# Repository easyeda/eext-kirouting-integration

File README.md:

# KiRouting Integration

[English](README_EN.md) | 中文

将 **KiCadRouting Tools**（Rust 加速 A* 自动布线引擎）桥接到 **嘉立创EDA专业版（EasyEDA Pro）** 的完整解决方案。

## 项目地址

| 项目 | 地址 | 说明 |
|------|------|------|
| 本项目（扩展 + 桥接服务器） | https://github.com/easyeda/eext-kirouting-integration | EasyEDA Pro 扩展及 Python 桥接服务器 |
| KiCadRouting Tools（布线引擎） | https://github.com/drandyhaas/KiCadRoutingTools/tree/main#command-line-interface | Rust 加速 A* 路由器（原项目） |

## 系统架构

```
┌─────────────────────┐     HTTP (localhost:8765)     ┌──────────────────────┐
│  EasyEDA Pro 编辑器  │ ◄──────────────────────────► │   Bridge Server      │
│  (嘉立创EDA专业版)    │                              │   (Python/FastAPI)   │
│                     │                              │                      │
│  ┌───────────────┐  │                              │  ┌────────────────┐  │
│  │ TypeScript 扩展│  │  ← 收集PCB数据 / 写回结果 →   │  │ 格式转换        │  │
│  │ (kirouting-   │  │                              │  │ EasyEDA ↔ KiCad│  │
│  │  integration) │  │                              │  └───────┬────────┘  │
│  └───────────────┘  │                              │          │           │
└─────────────────────┘                              │          ▼           │
                                                     │  ┌────────────────┐  │
                                                     │  │ KiCadRouting   │  │
                                                     │  │ Tools 布线引擎  │  │
                                                     │  │ (Python + Rust)│  │
                                                     │  └────────────────┘  │
                                                     └──────────────────────┘
```

## 快速开始（用户安装）

只需两步即可使用：

### 第一步：安装扩展

在 EasyEDA Pro（嘉立创EDA专业版）的 **扩展广场** 中搜索 **KiRouting Integration** 并安装。

也可以手动安装：从 [GitHub Releases](https://github.com/easyeda/eext-kirouting-integration/releases/latest) 下载 `.eext` 文件，在 **扩展** → **扩展管理器** → **从本地安装** 中导入。

> **重要**：安装后需在 EasyEDA Pro 设置中开启 **外部交互**（External Interaction）选项，否则扩展无法连接本地 KiRouting 服务。

### 第二步：获取启动脚本

从本项目仓库获取桥接服务器：

```bash
git clone https://github.com/easyeda/eext-kirouting-integration.git
```

或直接在 [项目页面](https://github.com/easyeda/eext-kirouting-integration) 点击 **Code** → **Download ZIP** 下载并解压。

启动脚本位于项目目录中的 `bridge_server/start_server.bat`。

### 第三步：启动桥接服务器

双击运行 `bridge_server/start_server.bat`，脚本会自动完成以下操作：

1. 检测 Python 环境，未安装则自动通过 winget 安装
2. 检测并安装 Python 依赖（fastapi、uvicorn、pydantic、numpy）
3. 检测 KiCadRoutingTools，不存在则自动从 GitHub 克隆
4. 检测 Rust 路由器编译产物，未编译则自动构建（无 Rust 环境时降级为纯 Python 模式）
5. 启动桥接服务器（监听 `http://localhost:8765`）

> 首次运行需要联网下载依赖，后续启动会跳过已完成的步骤。

### 第四步：开始使用

1. 打开一个 PCB 文件
2. 顶部菜单栏点击 **KiRouting自动布线** → **打开布线工具...**
3. 在弹出的对话框中选择网络、配置参数、点击 **开始布线**

4. 等待布线完成，结果自动写回 PCB

> 如果服务器未启动，扩展会弹出引导对话框，提供下载链接和操作说明。

## 布线功能

- **单端布线** — A* 寻路，支持 MPS 网络排序、拆线重布、总线检测
- **差分对布线** — 中心线 + 偏移，自动极性交换，GND 过孔放置
- **电源平面** — 自动过孔连接 SMD 焊盘到内层铜皮，Voronoi 分区
- **BGA 扇出** — 自动逃逸路径生成
- **QFN 扇出** — QFN/QFP 焊盘延伸
- **长度匹配** — DDR4 字节通道自动分组，蛇形走线
- **阻抗控制** — 根据叠层自动计算每层线宽
- **目标交换优化** — 匈牙利算法最小化交叉

## 布线工作流程（数据流）

```
1. 扩展从 EasyEDA Pro 读取 PCB 数据（元件、焊盘、网络、已有走线、板框）
       ↓
2. 大型元件列表分块发送 → POST /api/extra-components
       ↓
3. 完整 PCB 数据 + 布线参数 → POST /api/route
       ↓
4. 服务器格式转换：EasyEDA JSON → .kicad_pcb（坐标系、单位、层映射）
       ↓
5. 调用 KiCadRoutingTools 执行 A* 布线
       ↓
6. 对比输入/输出 .kicad_pcb，提取新增走线和过孔
       ↓
7. 转换回 EasyEDA 坐标系
       ↓
8. 扩展轮询 GET /api/status/{job_id} 等待完成
       ↓
9. 扩展获取结果 GET /api/result/{job_id}
       ↓
10. 将新走线/过孔写入 EasyEDA Pro PCB 编辑器
```

## API 接口

| 方法 | 路径 | 说明 |
|------|------|------|
| GET | `/api/test` | 健康检查，确认服务器运行 |
| POST | `/api/extra-components` | 分块发送大型元件列表 |
| POST | `/api/route` | 提交布线任务（异步，返回 job_id） |
| GET | `/api/status/{job_id}` | 查询任务状态 |
| GET | `/api/result/{job_id}` | 获取布线结果（走线 + 过孔） |
| POST | `/api/cancel/{job_id}` | 取消正在运行的任务 |
| GET | `/api/config/defaults` | 获取默认布线参数 |
| POST | `/api/analyze/board-summary` | 板卡概览分析 |
| POST | `/api/analyze/power-nets` | 电源网络分析 |
| POST | `/api/analyze/diff-pairs` | 差分对检测 |
| POST | `/api/analyze/bus-groups` | 总线组检测 |
| POST | `/api/analyze/net-stats` | 网络统计 |

## 开发者指南

以下内容面向需要修改源码或从源码构建的开发者。

### 目录结构

```
KICAD Routing-intergration/
├── KiCadRoutingTools/              # 布线引擎（Rust加速A*路由器）
│   ├── route.py                    # 单端布线 CLI
│   ├── route_diff.py               # 差分对布线 CLI
│   ├── route_planes.py             # 电源/地平面 CLI
│   ├── rust_router/                # Rust A* 实现
│   └── ...
├── kirouting-integration/           # EasyEDA Pro 扩展 + 桥接服务器
│   ├── src/index.ts                # 扩展入口（TypeScript）
│   ├── iframe/                     # 扩展 UI（参数配置对话框）
│   ├── bridge_server/              # Python 桥接服务器
│   │   ├── server.py               # FastAPI 服务（端口 8765）
│   │   ├── start_server.bat        # 一键启动脚本（自动安装依赖）
│   │   ├── routing_runner.py       # 布线调度（调用 KiCadRoutingTools）
│   │   ├── easyeda_to_kicad.py     # EasyEDA JSON → KiCad 格式转换
│   │   ├── kicad_diff.py           # 对比输入/输出提取新走线
│   │   ├── coord_transform.py      # 坐标系转换（mil ↔ mm）
│   │   ├── layer_mapping.py        # 层映射（EasyEDA ↔ KiCad）
│   │   ├── models.py               # Pydantic 数据模型
│   │   ├── analysis.py             # AI 分析（电源网络、差分对等）
│   │   └── requirements.txt        # Python 依赖
│   ├── extension.json              # 扩展清单
│   ├── package.json                # Node.js 项目配置
│   └── tsconfig.json               # TypeScript 配置
└── README.md                       # 本文件
```

### 环境要求

| 组件 | 版本要求 | 用途 |
|------|---------|------|
| Python | 3.8+ | 桥接服务器 |
| Node.js | 20.5.0+ | 编译扩展 |
| Rust | stable | 编译路由器（可选，无则降级为纯 Python） |
| EasyEDA Pro | 2.3.0+ | 运行扩展 |

### 开发命令

```bash
# === 扩展开发 ===
cd kirouting-integration
npm install                  # 安装前端依赖
npm run compile              # 编译 TypeScript
npm run build                # 编译 + 打包 .eext
npm run fix                  # 代码格式化 + lint

# === 桥接服务器 ===
cd kirouting-integration/bridge_server
pip install -r requirements.txt  # 安装 Python 依赖
python server.py                 # 启动服务器

# === 布线引擎 ===
cd KiCadRoutingTools
python build_router.py       # 编译 Rust 路由器（不要直接 cargo build）

# === 测试 ===
cd KiCadRoutingTools
python tests/test_fanout_and_route.py --all        # 完整集成测试
python tests/test_fanout_and_route.py --all --quick  # 快速模式

# === 验证 ===
cd KiCadRoutingTools
python check_drc.py output.kicad_pcb               # DRC 检查
python check_connected.py output.kicad_pcb         # 连通性检查
```

## 注意事项

- 桥接服务器同一时间只能运行一个布线任务，提交新任务会自动取消上一个
- 板框间距（board_edge_clearance）建议 ≥ 0.5mm，避免阶梯状走线
- 单位转换链路：EasyEDA UI (mm) → 扩展内部 (mil) → 服务器 (mil→mm) → 布线引擎 (mm)
- 修改 Rust 路由器后需要在 `rust_router/Cargo.toml` 中更新版本号

## 许可证

- KiCadRoutingTools: MIT License
- kirouting-integration: Apache-2.0 License

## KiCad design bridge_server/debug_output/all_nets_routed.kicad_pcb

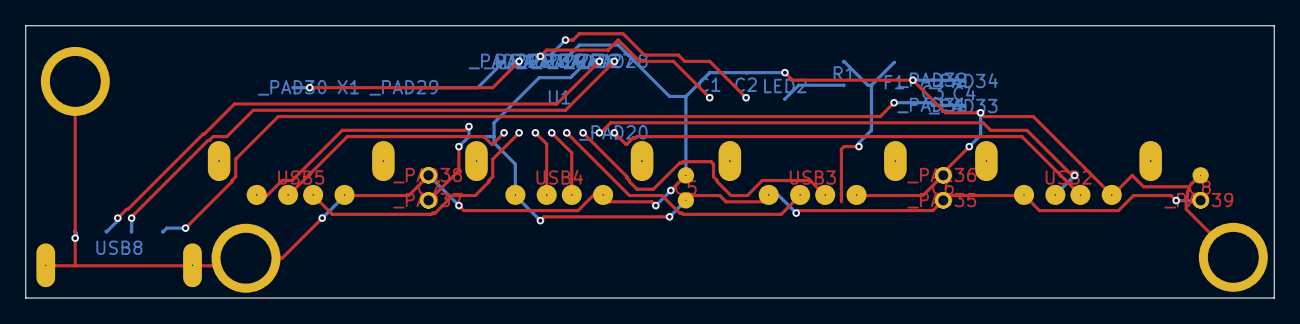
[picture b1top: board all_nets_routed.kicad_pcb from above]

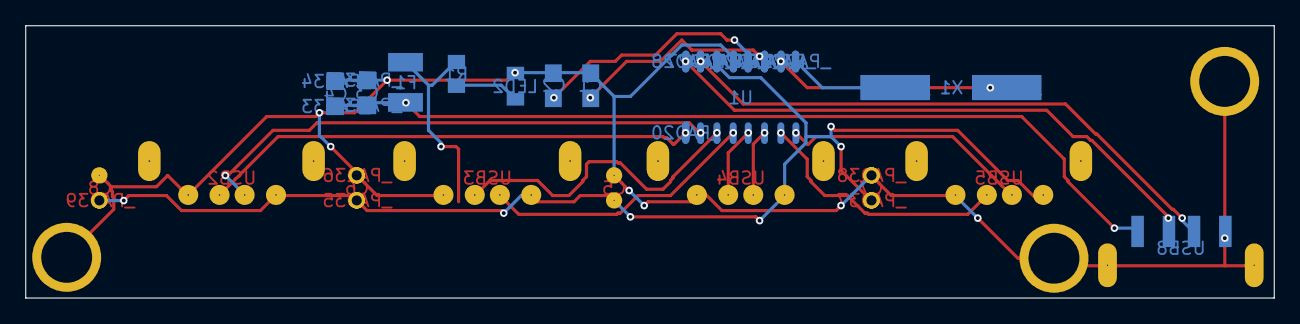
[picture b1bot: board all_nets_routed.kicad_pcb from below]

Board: 2 copper layers, 99.6 x 21.7 mm, 41 parts (25 on the bottom side), 18 nets.

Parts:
C1: C1
C2: C2
C3: C3
C4: C4
C5: C5
C6: C6
C7: C7
C8: C8
F1: F1
LED2: LED2
R1: R1
U1: U1
USB2: USB2
USB3: USB3
USB4: USB4
USB5: USB5
USB8: USB8
X1: X1
_PAD0: _PAD0
_PAD1: _PAD1
_PAD2: _PAD2
_PAD20: _PAD20
_PAD21: _PAD21
_PAD22: _PAD22
_PAD23: _PAD23
_PAD24: _PAD24
_PAD25: _PAD25
_PAD26: _PAD26
_PAD27: _PAD27
_PAD28: _PAD28
_PAD29: _PAD29
_PAD30: _PAD30
_PAD31: _PAD31
_PAD32: _PAD32
_PAD33: _PAD33
_PAD34: _PAD34
_PAD35: _PAD35
_PAD36: _PAD36
_PAD37: _PAD37
_PAD38: _PAD38
_PAD39: _PAD39

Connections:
$1N1537: LED2.1, R1.1
+5V: C5.1, C6.1, C7.1, C8.1, F1.1, R1.2, U1.11, USB2.1, USB3.1, USB4.1, USB5.1, _PAD26.11, _PAD35.1, _PAD37.1, _PAD39.1
DM: U1.9, USB8.2, _PAD28.9
DM1: U1.7, USB2.2
DM2: U1.5, USB3.2
DM3: U1.3, USB4.2
DM4: U1.1, USB5.2
DP: U1.10, USB8.3, _PAD27.10
DP1: U1.8, USB2.3, _PAD20.8
DP2: U1.6, USB3.3
DP3: U1.4, USB4.3
DP4: U1.2, USB5.3
GND: C1.2, C2.2, C3.1, C4.1, C5.2, C6.2, C7.2, C8.2, LED2.2, U1.12, USB2.4, USB3.4, USB4.4, USB5.4, USB8.4, USB8.5, _PAD0.3, _PAD1.3, _PAD2.3, _PAD25.12, _PAD32.1, _PAD34.1, _PAD36.2, _PAD38.2
VBUS: C3.2, C4.2, F1.2, USB8.1, _PAD31.2, _PAD33.2
VDD18: C1.1, U1.14, _PAD23.14
VDD33: C2.1, U1.13, _PAD24.13
XIN: U1.16, X1.2, _PAD21.16, _PAD29.2
XOUT: U1.15, X1.1, _PAD22.15, _PAD30.1

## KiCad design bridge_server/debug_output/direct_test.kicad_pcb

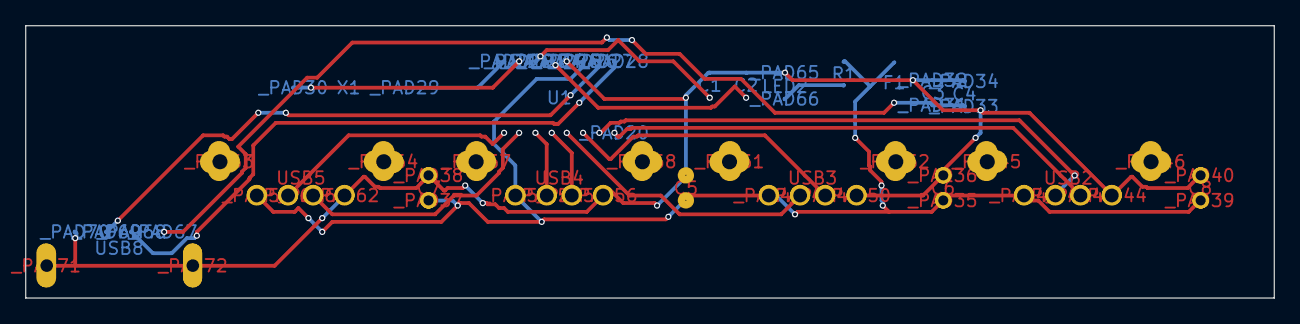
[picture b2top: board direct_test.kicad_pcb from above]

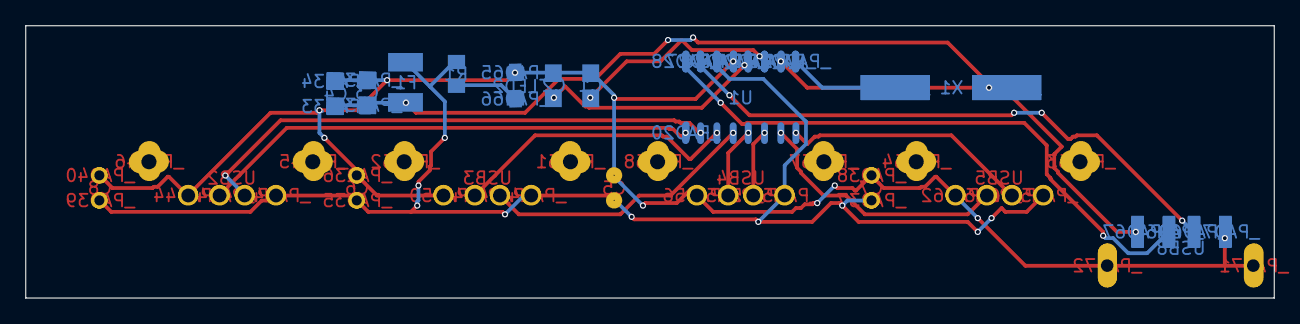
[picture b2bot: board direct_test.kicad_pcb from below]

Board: 2 copper layers, 99.6 x 21.7 mm, 71 parts (31 on the bottom side), 18 nets.

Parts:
C1: C1
C2: C2
C3: C3
C4: C4
C5: C5
C6: C6
C7: C7
C8: C8
F1: F1
LED2: LED2
R1: R1
U1: U1
USB2: USB2
USB3: USB3
USB4: USB4
USB5: USB5
USB8: USB8
X1: X1
_PAD20: _PAD20
_PAD21: _PAD21
_PAD22: _PAD22
_PAD23: _PAD23
_PAD24: _PAD24
_PAD25: _PAD25
_PAD26: _PAD26
_PAD27: _PAD27
_PAD28: _PAD28
_PAD29: _PAD29
_PAD30: _PAD30
_PAD31: _PAD31
_PAD32: _PAD32
_PAD33: _PAD33
_PAD34: _PAD34
_PAD35: _PAD35
_PAD36: _PAD36
_PAD37: _PAD37
_PAD38: _PAD38
_PAD39: _PAD39
_PAD40: _PAD40
_PAD41: _PAD41
_PAD42: _PAD42
_PAD43: _PAD43
_PAD44: _PAD44
_PAD45: _PAD45
_PAD46: _PAD46
_PAD47: _PAD47
_PAD48: _PAD48
_PAD49: _PAD49
_PAD50: _PAD50
_PAD51: _PAD51
_PAD52: _PAD52
_PAD53: _PAD53
_PAD54: _PAD54
_PAD55: _PAD55
_PAD56: _PAD56
_PAD57: _PAD57
_PAD58: _PAD58
_PAD59: _PAD59
_PAD60: _PAD60
_PAD61: _PAD61
_PAD62: _PAD62
_PAD63: _PAD63
_PAD64: _PAD64
_PAD65: _PAD65
_PAD66: _PAD66
_PAD67: _PAD67
_PAD68: _PAD68
_PAD69: _PAD69
_PAD70: _PAD70
_PAD71: _PAD71
_PAD72: _PAD72

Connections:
$1N1537: LED2.1, R1.1, _PAD66.1
+5V: C5.1, C6.1, C7.1, C8.1, F1.1, R1.2, U1.11, USB2.1, USB3.1, USB4.1, USB5.1, _PAD26.11, _PAD35.1, _PAD37.1, _PAD39.1, _PAD41.1, _PAD47.1, _PAD53.1, _PAD59.1
DM: U1.9, USB8.2, _PAD28.9, _PAD68.2
DM1: U1.7, USB2.2, _PAD42.2
DM2: U1.5, USB3.2, _PAD48.2
DM3: U1.3, USB4.2, _PAD54.2
DM4: U1.1, USB5.2, _PAD60.2
DP: U1.10, USB8.3, _PAD27.10, _PAD69.3
DP1: U1.8, USB2.3, _PAD20.8, _PAD43.3
DP2: U1.6, USB3.3, _PAD49.3
DP3: U1.4, USB4.3, _PAD55.3
DP4: U1.2, USB5.3, _PAD61.3
GND: C1.2, C2.2, C3.1, C4.1, C5.2, C6.2, C7.2, C8.2, LED2.2, U1.12, USB2.4, USB3.4, USB4.4, USB5.4, USB8.4, USB8.5, _PAD25.12, _PAD32.1, _PAD34.1, _PAD36.2, _PAD38.2, _PAD40.2, _PAD44.4, _PAD50.4, _PAD56.4, _PAD62.4, _PAD65.2, _PAD70.4, _PAD71.5, _PAD72.5
VBUS: C3.2, C4.2, F1.2, USB8.1, _PAD31.2, _PAD33.2, _PAD67.1
VDD18: C1.1, U1.14, _PAD23.14
VDD33: C2.1, U1.13, _PAD24.13
XIN: U1.16, X1.2, _PAD21.16, _PAD29.2
XOUT: U1.15, X1.1, _PAD22.15, _PAD30.1

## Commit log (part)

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2026-05-11 第一次提交
2026-05-11 Initial local state before merge
2026-05-21 Clean up tracked files and update extension
    - Remove __pycache__ and debug_output from tracking (already in .gitignore)
    - Remove build_exe.bat
    - Add service-not-found.html iframe page
    - Update extension source, locales, and dist
2026-05-22 Update startup script to self-download mode
    - Embed start_server.bat content directly in service-not-found.html
    - Script downloads Python files via curl instead of requiring zip/git clone
    - KiCadRoutingTools fetched as zip archive instead of full git clone
    - Remove Rust router check for faster startup
    - Remove old .eext build artifacts from tracking
2026-05-22 Download server files into subfolder and remove Rust router check
    - Start script creates bridge_server/ subfolder for Python files
    - Embedded BAT in HTML updated to match
    - Remove Rust router build step for faster startup
    - Add local artifacts to .edaignore to prevent bloated .eext
2026-05-22 Fix powershell not found on some systems
    Use full path %SystemRoot%\System32\WindowsPowerShell\v1.0\powershell.exe
    instead of bare 'powershell' which may not be in PATH.
2026-05-22 Add tar fallback for zip extraction
    Try PowerShell Expand-Archive first, fall back to tar (Win10 1803+)
    if PowerShell is unavailable.
2026-05-22 Fix KiCadRoutingTools path resolution and polygon pad handling
    - routing_runner.py, kicad_diff.py, analysis.py: search both ../KiCadRoutingTools
    and ../../KiCadRoutingTools to support both dev and user download layouts
    - index.ts: handle polygon pads where pad data is [shape, [points...]]
    instead of [shape, width, height] - compute bounding box for width/height
2026-05-22 Add debug logging to routing job for troubleshooting
    Logs KICAD_TOOLS_DIR path, sys.path, route.py existence,
    and full traceback on failure to server console.
2026-05-22 Require Rust router for acceptable routing speed
    Rust router is not optional - pure Python A* is too slow for real boards.
    Script now checks for cargo, builds rust_astar_router.pyd, and exits
    with instructions if Rust is not installed.
2026-05-22 Fix silent thread death when Rust router is not built
    - route.py calls sys.exit(1) if Rust module missing, which raises
    SystemExit (not Exception) and silently kills the routing thread
    - server.py: catch BaseException to handle SystemExit
    - routing_runner.py: wrap route imports in try/except SystemExit
    and convert to RuntimeError with clear error message
    - index.ts: fetch error details from server when status is failed
2026-05-22 Fix polygon pad SVG path parsing causing giant obstacles
    Polygon pad data contains SVG commands like 'L','M' mixed with numbers.
    Previous code treated every 2 elements as x,y pairs, causing non-numeric
    values to be read as 0 and producing incorrect bounding boxes.
    Now filters to only numeric values before computing bounding box.
2026-05-25 Redesign service-not-found page and update extension
    - Redesign bridge server not-running page with cleaner UI (referencing kipida-integration style)
    - Embed start_server.bat content directly in HTML, download as ZIP to avoid browser blocking
    - Add i18n support (zh/en) with auto language detection
    - Remove bridge_server Python files from repo (downloaded at runtime by start_server.bat)
    - Update extension UI and routing logic
2026-05-25 Add built .eext package
2026-05-25 Fix downloaded bat script by using base64 encoding
    The JS string escaping was corrupting the bat content, causing it to
    exit immediately when run. Now the bat content is stored as base64 and
    decoded at download time, ensuring byte-perfect CRLF output.
2026-05-25 Fix bat script base64 encoding from original source file
    Previous base64 was hand-crafted with incorrect escape sequences
    (double-caret ^^>^^& instead of ^>^&1) causing cmd.exe parse errors.
    Now generated directly from the original start_server.bat with proper
    LF-to-CRLF conversion.
2026-05-25 Restore bridge_server Python files to repo
    The startup script downloads these files from GitHub raw URLs.
    They were accidentally removed, causing 404 errors that got saved
    as Python files, resulting in SyntaxError on startup.
2026-05-29 ci: add GitHub Actions build workflow
    Added for multi-language support
2026-05-29 ci: update GitHub Actions build workflow
    Updated for multi-language support
2026-06-05 feat: 自动化完成多语言翻译
2026-06-05 chore: 修正多语言配置
2026-06-16 docs: 创建英文README
2026-06-17 feat: 添加Linux/macOS启动脚本，下载按钮改为多平台选择
    - 新增 bridge_server/start_server.sh (Linux/macOS一键启动脚本)
    - service-not-found页面按钮改为竖向排布
    - 下载按钮拆分为 Windows/Linux/macOS 三个按钮
    - 每个脚本以ZIP压缩包方式下载，避免浏览器拦截
    - ZIP中为.sh文件设置了Unix可执行权限(0755)
    - 新增 generate_html.py 用于脚本变更后重新生成HTML
2026-06-17 fix: 修正start_server.bat中Rust路由器检测逻辑
    - 修正检测文件名: rust_astar_router.pyd → grid_router.pyd
    - 移除不必要的cargo前置检查，直接调用build_router.py
    - build_router.py已支持下载预编译二进制，无需Rust工具链
    - 与start_server.sh逻辑对齐
2026-06-17 chore: 更新.eext编译产物至v1.0.1
